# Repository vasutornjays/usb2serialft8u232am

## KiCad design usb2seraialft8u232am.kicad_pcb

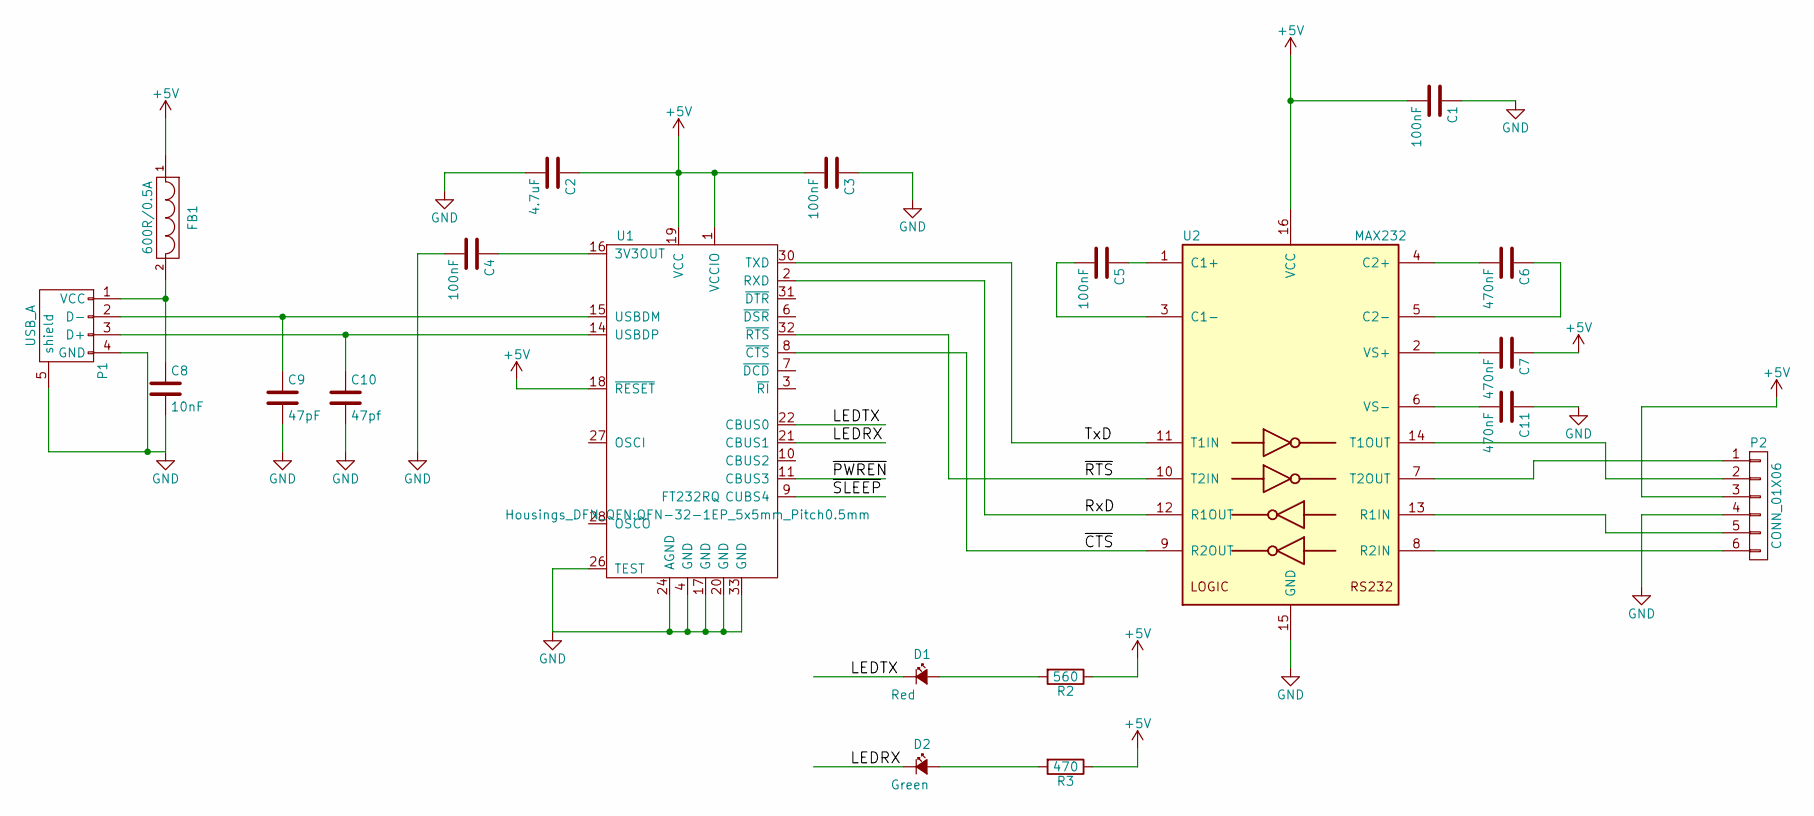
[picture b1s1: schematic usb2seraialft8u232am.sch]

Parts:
C1, C3, C4, C5: 100nF; C_0603
C2: 4.7uF; C_0603
C6, C7, C11: 470nF; C_0603
C8: 10nF; C_0603
C9: 47pF; C_0603
C10: 47pf; C_0603
D1: Red; LED_0603
D2: Green; LED_0603
FB1: 600R/0.5A; C_0805
P1: USB_A; USB-A-PLUG_UDRA04MTKNN
P2: CONN_01X06; Pin_Header_Angled_1x06
R2: 560; R_0603
R3: 470; R_0603
U1: FT232RQ; QFN-32-1EP_5x5mm_Pitch0.5mm
U2: MAX232; SOIC-16_3.9x9.9mm_Pitch1.27mm

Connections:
+5V: C1.2, C2.1, C3.2, C7.1, FB1.1, P2.3, R2.1, R3.1, U1.1 (VCCIO), U1.18 (~RESET~), U1.19 (VCC), U2.16 (VCC)
/LEDRX: D2.1 (K), U1.21 (CBUS1)
/LEDTX: D1.1 (K), U1.22 (CBUS0)
/RxD: U1.2 (RXD), U2.12 (R1OUT)
/TxD: U1.30 (TXD), U2.11 (T1IN)
/~CTS~: U1.8 (~CTS~), U2.9 (R2OUT)
/~PWREN~: U1.11 (CBUS3)
/~RTS~: U1.32 (~RTS~), U2.10 (T2IN)
/~SLEEP~: U1.9 (CUBS4)
GND: C1.1, C2.2, C3.1, C4.2, C8.2, C9.2, C10.2, C11.1, P1.4 (GND), P1.5 (shield), P2.4, U1.4 (GND), U1.17 (GND), U1.20 (GND), U1.24 (AGND), U1.26 (TEST), U1.33 (GND), U2.15 (GND)
unnamed: C4.1, U1.16 (3V3OUT)
unnamed: C5.1, U2.1 (C1+)
unnamed: C5.2, U2.3 (C1-)
unnamed: C6.1, U2.5 (C2-)
unnamed: C6.2, U2.4 (C2+)
unnamed: C7.2, U2.2 (VS+)
unnamed: C8.1, FB1.2, P1.1 (VCC)
unnamed: C9.1, P1.2 (D-), U1.15 (USBDM)
unnamed: C10.1, P1.3 (D+), U1.14 (USBDP)
unnamed: C11.2, U2.6 (VS-)
unnamed: D1.2 (A), R2.2
unnamed: D2.2 (A), R3.2
unnamed: P2.1, U2.7 (T2OUT)
unnamed: P2.2, U2.14 (T1OUT)
unnamed: P2.5, U2.13 (R1IN)
unnamed: P2.6, U2.8 (R2IN)

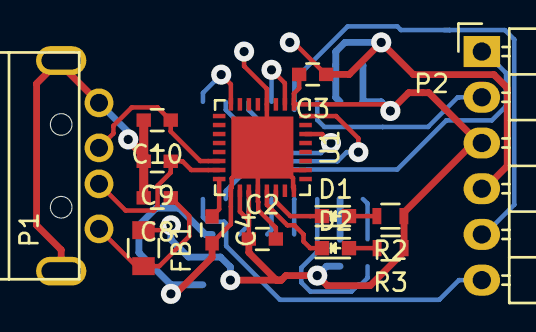
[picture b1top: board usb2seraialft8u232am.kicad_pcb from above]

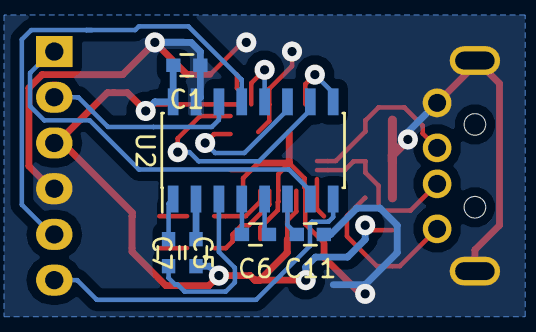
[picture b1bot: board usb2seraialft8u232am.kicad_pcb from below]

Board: 2 copper layers, 20 parts (6 on the bottom side), 24 nets.

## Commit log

2016-10-30 :octocat: Added .gitattributes & .gitignore files
2016-10-30 usb2serialft8u232am ver1
    prototype
2016-10-30 change USB to PLUG USB
2016-10-31 new PCB design
